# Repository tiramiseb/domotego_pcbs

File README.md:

Domotego PCBs
=============

As the owner of the Domotego online shop, I develop small useful companion
boards helping with DIY home automation.

The shop
--------

Domotego is an online shop dedicated to DIY home automation.
In order to maintain a simple and effective offer, the shop focuses on the
_Calaos_ Open Source home automation solution.

* Domotego: https://www.domotego.com/
* Calaos: https://calaos.fr/

License
-------

All those boards are licensed under the _Creative Commons
Attribution-ShareAlike 4.0_ license.

https://creativecommons.org/licenses/by-sa/4.0/

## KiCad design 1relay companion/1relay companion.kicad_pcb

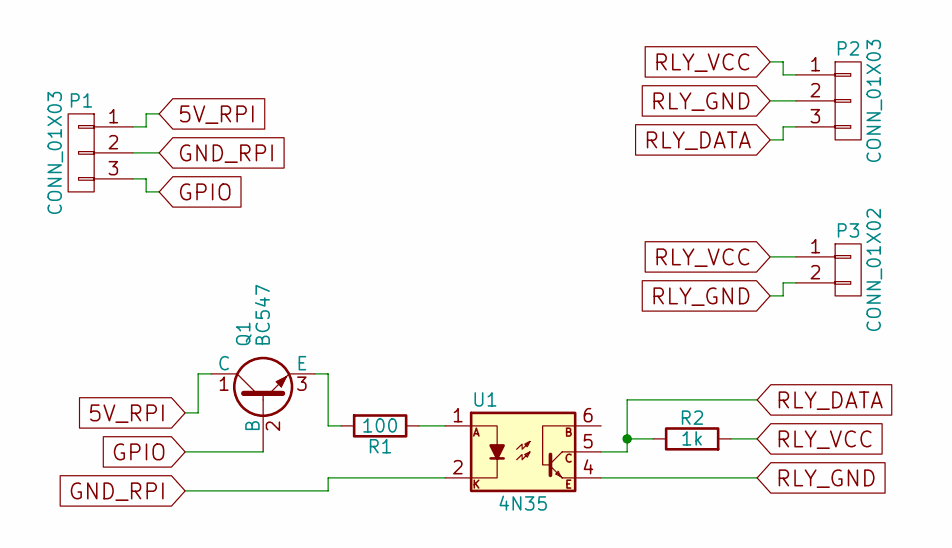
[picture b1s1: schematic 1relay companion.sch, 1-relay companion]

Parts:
P1: CONN_01X03; Pin_Header_Straight_1x03
P2: CONN_01X03; Socket_Strip_Straight_1x03
P3: CONN_01X02; Pin_Header_Straight_1x02
Q1: BC547; TO-92_Inline_Narrow_Oval
R1: 100; Resistor_Horizontal_RM10mm
R2: 1k; Resistor_Horizontal_RM10mm
U1: 4N35; DIP-6_W7.62mm

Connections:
5V_RPI: P1.1, Q1.1 (C)
GND_RPI: P1.2, U1.2
GPIO: P1.3, Q1.2 (B)
unnamed: Q1.3 (E), R1.2
unnamed: R1.1, U1.1
RLY_DATA: P2.3, R2.1, U1.5
RLY_GND: P2.2, P3.2, U1.4
RLY_VCC: P2.1, P3.1, R2.2

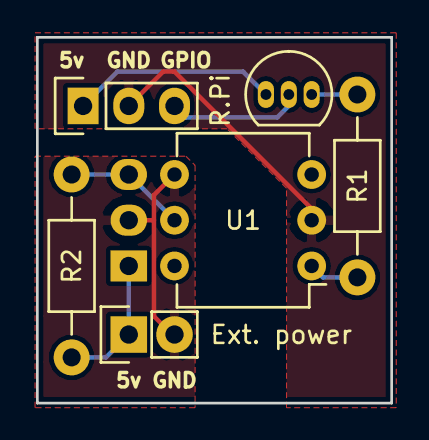
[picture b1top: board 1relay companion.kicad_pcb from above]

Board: 2 copper layers, 19.7 x 20.3 mm, 7 parts (1 on the bottom side), 8 nets.

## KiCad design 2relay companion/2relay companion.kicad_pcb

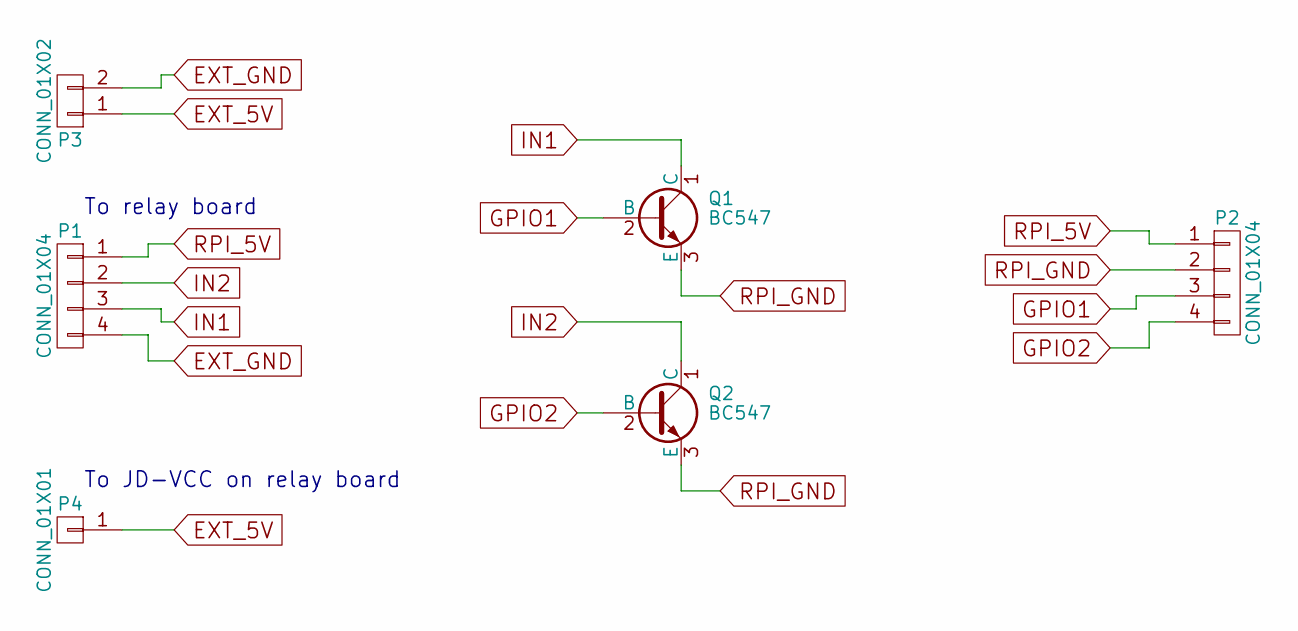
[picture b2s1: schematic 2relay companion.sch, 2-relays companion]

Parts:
P1: CONN_01X04; Socket_Strip_Straight_1x04
P2: CONN_01X04; Pin_Header_Straight_1x04
P3: CONN_01X02; Pin_Header_Straight_1x02
P4: CONN_01X01; SolderWirePad_single_1-5mmDrill
Q1, Q2: BC547; TO-92_Inline_Narrow_Oval

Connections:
EXT_5V: P3.1, P4.1
EXT_GND: P1.4, P3.2
GPIO1: P2.3, Q1.2 (B)
GPIO2: P2.4, Q2.2 (B)
IN1: P1.3, Q1.1 (C)
IN2: P1.2, Q2.1 (C)
RPI_5V: P1.1, P2.1
RPI_GND: P2.2, Q1.3 (E), Q2.3 (E)

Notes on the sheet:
To relay board
To JD-VCC on relay board

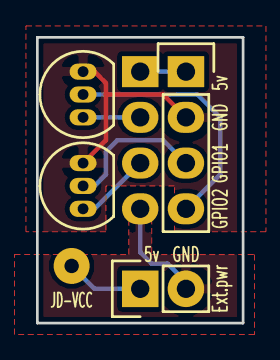
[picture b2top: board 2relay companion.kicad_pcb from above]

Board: 2 copper layers, 11.4 x 15.9 mm, 6 parts (1 on the bottom side), 8 nets.

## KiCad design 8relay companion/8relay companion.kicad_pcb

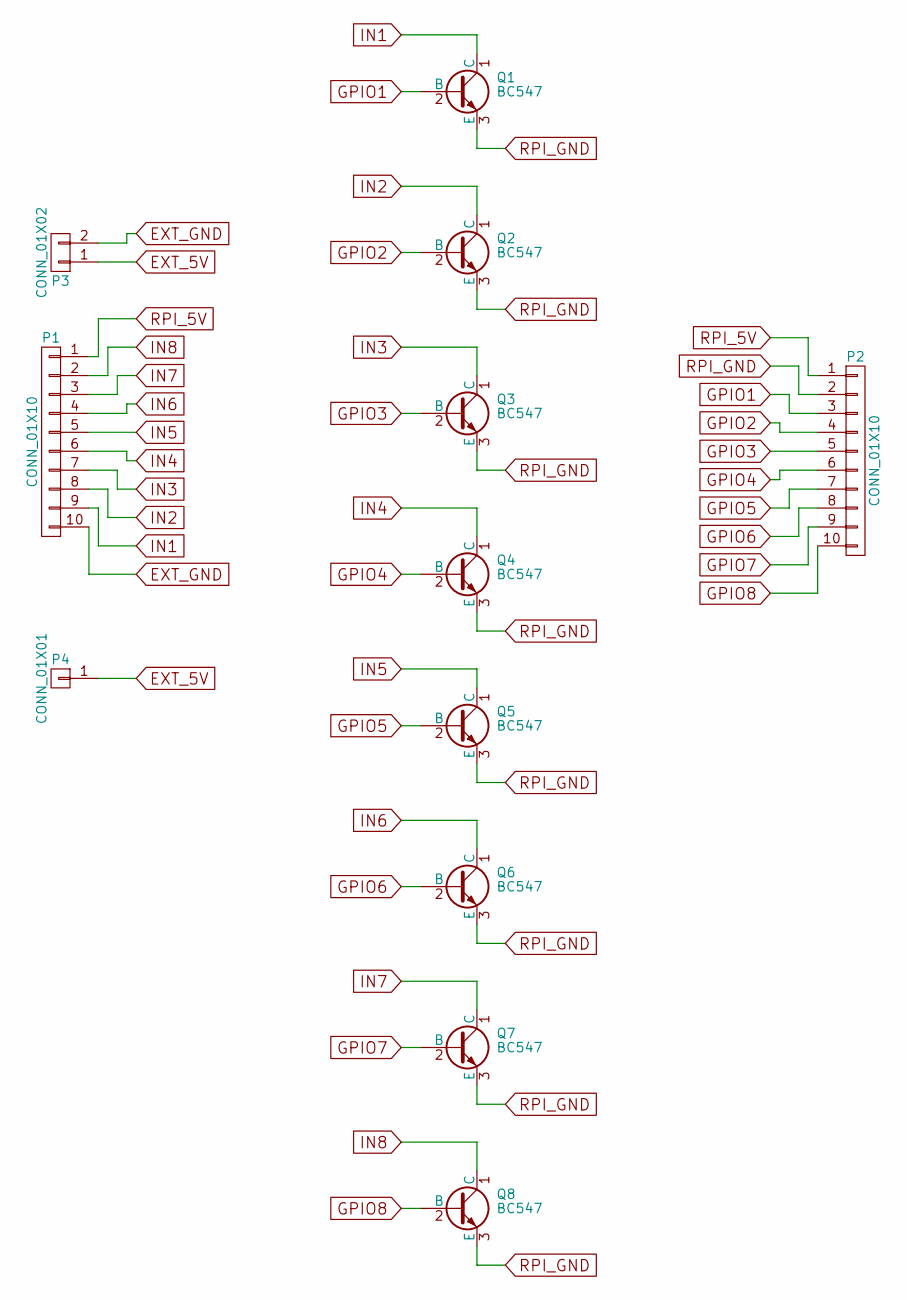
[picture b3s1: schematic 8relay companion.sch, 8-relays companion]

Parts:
P1: CONN_01X10; Socket_Strip_Straight_1x10
P2: CONN_01X10; Pin_Header_Straight_1x10
P3: CONN_01X02; Pin_Header_Straight_1x02
P4: CONN_01X01; SolderWirePad_single_0-8mmDrill
Q1, Q2, Q3, Q4, Q5, Q6, Q7, Q8: BC547; TO-92_Inline_Narrow_Oval

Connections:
EXT_5V: P3.1, P4.1
EXT_GND: P1.10, P3.2
GPIO1: P2.3, Q1.2 (B)
GPIO2: P2.4, Q2.2 (B)
GPIO3: P2.5, Q3.2 (B)
GPIO4: P2.6, Q4.2 (B)
GPIO5: P2.7, Q5.2 (B)
GPIO6: P2.8, Q6.2 (B)
GPIO7: P2.9, Q7.2 (B)
GPIO8: P2.10, Q8.2 (B)
IN1: P1.9, Q1.1 (C)
IN2: P1.8, Q2.1 (C)
IN3: P1.7, Q3.1 (C)
IN4: P1.6, Q4.1 (C)
IN5: P1.5, Q5.1 (C)
IN6: P1.4, Q6.1 (C)
IN7: P1.3, Q7.1 (C)
IN8: P1.2, Q8.1 (C)
RPI_5V: P1.1, P2.1
RPI_GND: P2.2, Q1.3 (E), Q2.3 (E), Q3.3 (E), Q4.3 (E), Q5.3 (E), Q6.3 (E), Q7.3 (E), Q8.3 (E)

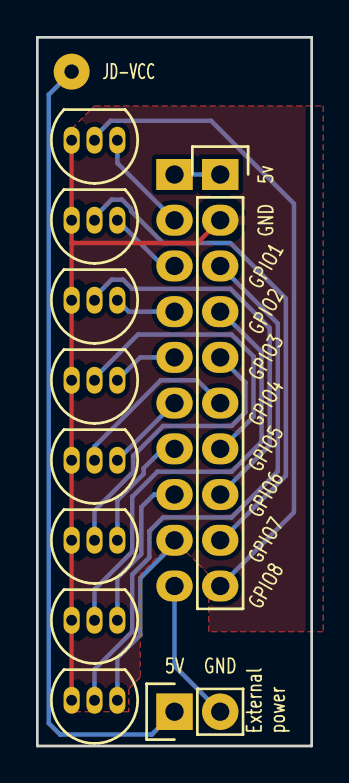
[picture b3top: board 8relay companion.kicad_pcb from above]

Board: 2 copper layers, 15.2 x 39.4 mm, 12 parts (1 on the bottom side), 20 nets.

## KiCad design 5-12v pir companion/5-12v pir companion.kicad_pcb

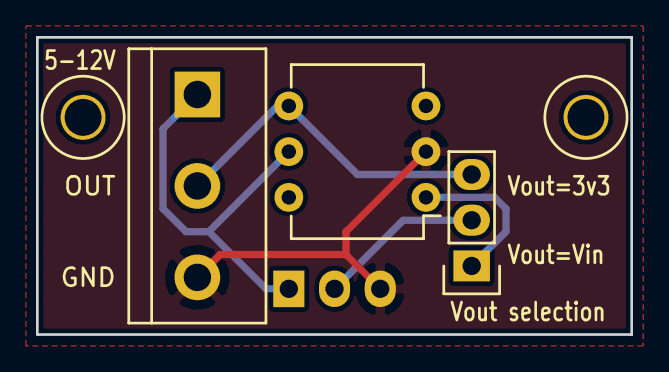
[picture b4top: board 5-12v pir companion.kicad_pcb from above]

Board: 2 copper layers, 33.0 x 16.5 mm, 4 parts (1 on the bottom side), 5 nets.

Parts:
P1: CONN_01X03; Socket_Strip_Straight_1x03
P2: CONN_01X03; bornier3
P3: CONN_01X03; Pin_Header_Straight_1x03
U1: 4N35; DIP-6_W7.62mm

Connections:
/Vout=Vin: P3.1, U1.1
GND: P1.3, P2.3, U1.2
HCSR501_OUT: P1.2, P3.2
HCSR501_VCC: P1.1, P2.1, U1.5
TRIGGER_OUT: P2.2, P3.3, U1.4

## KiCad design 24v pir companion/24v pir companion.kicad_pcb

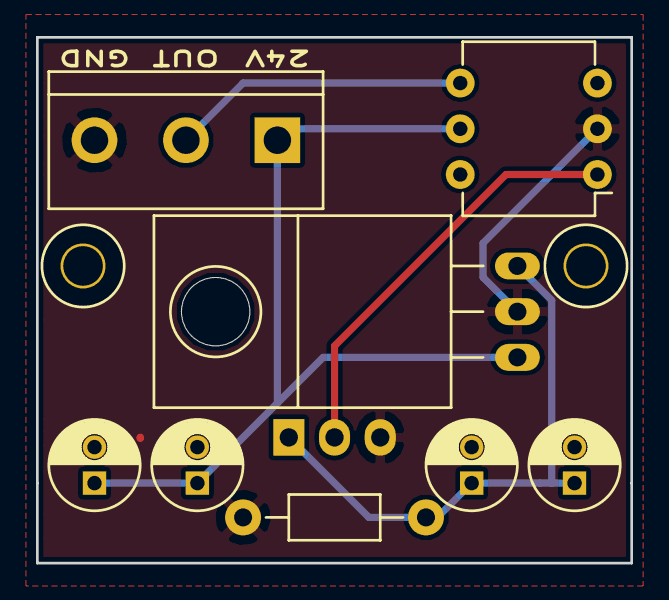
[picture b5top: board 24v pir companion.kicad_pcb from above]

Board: 2 copper layers, 33.0 x 29.2 mm, 9 parts (1 on the bottom side), 5 nets.

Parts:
C1, C3: 0.1µF; C_Radial_D5_L11_P2
C2, C4: 2.2µF; C_Radial_D5_L11_P2
P1: CONN_01X03; Socket_Strip_Straight_1x03
P2: CONN_01X03; bornier3
R1: 2.2k; Resistor_Horizontal_RM10mm
U1: LM7812; TO-220_Neutral123_Horizontal
U2: 4N35; DIP-6_W7.62mm

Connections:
GND: C1.2, C2.2, C3.2, C4.2, P1.3, P2.3, R1.2, U1.2, U2.2
HCSR501_OUT: P1.2, U2.1
HCSR501_VCC: C3.1, C4.1, P1.1, R1.1, U1.3
TRIGGER_OUT: P2.2, U2.4
VCC_15-35V: C1.1, C2.1, P2.1, U1.1, U2.5

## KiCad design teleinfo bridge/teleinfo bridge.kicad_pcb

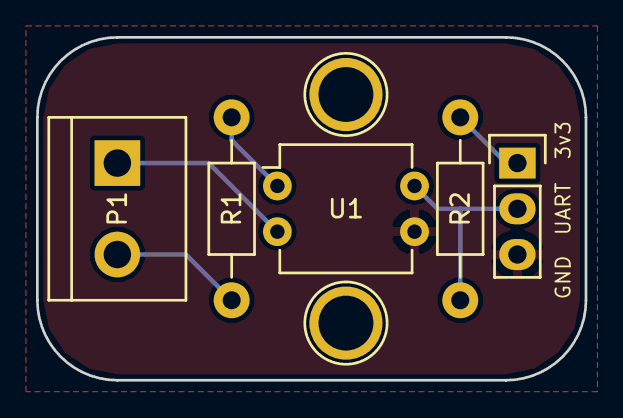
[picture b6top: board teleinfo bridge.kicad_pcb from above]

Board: 2 copper layers, 30.5 x 19.1 mm, 6 parts (1 on the bottom side), 6 nets.

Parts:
OSHW: Symbol_OSHW-Logo_SilkScreen
P1: CONN_01X02; bornier2
P2: CONN_01X03; Pin_Header_Straight_1x03
R1: 1.2k; Resistor_Horizontal_RM10mm
R2: 3.3k; Resistor_Horizontal_RM10mm
U1: SFH620A; DIP-4_W7.62mm

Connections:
GNDREF: P2.3, U1.3
unnamed: P1.1, U1.2
unnamed: P1.2, R1.2
unnamed: P2.1, R2.1
unnamed: P2.2, R2.2, U1.4
unnamed: R1.1, U1.1

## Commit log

2016-02-20 First README
2016-02-20 Better README formatting
2016-08-11 Publish the Teleinfo Brige schematics
2016-08-23 Publish the PIR companions
2016-09-06 Publish relay companions

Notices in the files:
1relay companion/1relay companion.kicad_pcb:
CC BY-SA
